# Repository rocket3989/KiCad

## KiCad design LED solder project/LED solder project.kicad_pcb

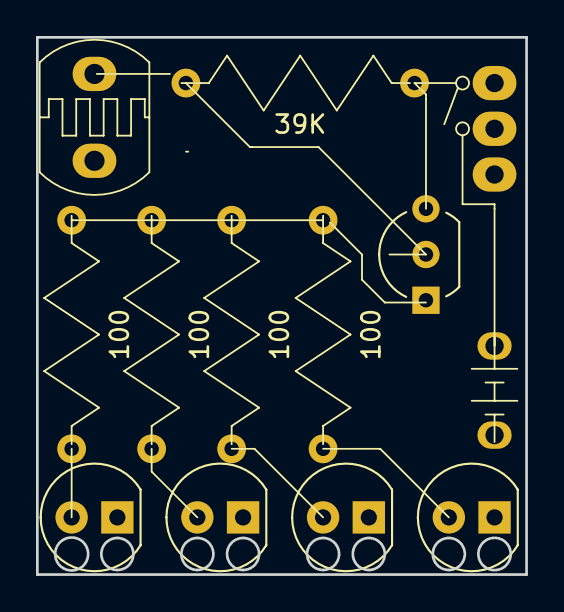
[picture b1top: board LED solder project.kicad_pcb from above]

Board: 2 copper layers, 27.2 x 29.8 mm, 13 parts (0 on the bottom side), 9 nets, no tracks yet.

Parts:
39K, 100, 100#2, 100#3, 100#4: R; resistor
BT1: Battery
D1, D2, D3, D4: LED
Q1: PN2222A; transistor
R2: R_PHOTO; Photoresistor
SW1: SW_SPST; Switch

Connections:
GND: BT1.2, D1.1, D2.1, D3.1, R2.2
unnamed: 100.2, D1.2
unnamed: 100#2.2, D2.2
unnamed: 100#3.2, D3.2
unnamed: 100#4.2, D4.2
unnamed: 100.1, 100#2.1, 100#3.1, 100#4.1, Q1.1
unnamed: 39K.1, Q1.2, R2.1
unnamed: 39K.2, Q1.3, SW1.1
VCC: BT1.1, SW1.2

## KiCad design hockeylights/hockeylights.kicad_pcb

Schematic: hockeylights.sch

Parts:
D1: IR204A; LED_D3.0mm
D2: D_Photo; LED_D3.0mm
J1: I2C in; Socket_Strip_Straight_1x04_Pitch2.54mm
J2: I2C out; Socket_Strip_Straight_1x04_Pitch2.54mm
R1, R2: R; R_Axial_DIN0204_L3.6mm_D1.6mm_P5.08mm_Horizontal
U1: ATTINY85-20SU; DIP-8_W7.62mm_Socket_LongPads
U2, U3: WS2812; LED_D5.0mm-4

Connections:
GND: J1.4, J2.4, R1.2, R2.2, U1.4 (GND), U2.2, U3.2
unnamed: D1.1 (K), R1.1
unnamed: D1.2 (A), U1.6 (PB1(MISO/DO/AIN1/OC0B/OC1A/PCINT1))
unnamed: D2.2 (A), R2.1, U1.2 (PB3(XTAL1/CLKI/~OC1B~/ADC3/PCINT3))
unnamed: J1.2, J2.2, U1.5 (PB0(MOSI/DI/SDA/AIN0/OC0A/~OC1A~/AREF/P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)
unnamed: J1.3, J2.3, U1.7 (PB2(SCK/USCK/SCL/T0/INT0/ADC1/PCINT2))
unnamed: U1.3 (PB4(XTAL2/CLKO/OC1B/ADC2/PCINT4)), U2.1
unnamed: U2.4, U3.1
VCC: D2.1 (K), J1.1, J2.1, U1.8 (VCC), U2.3, U3.3

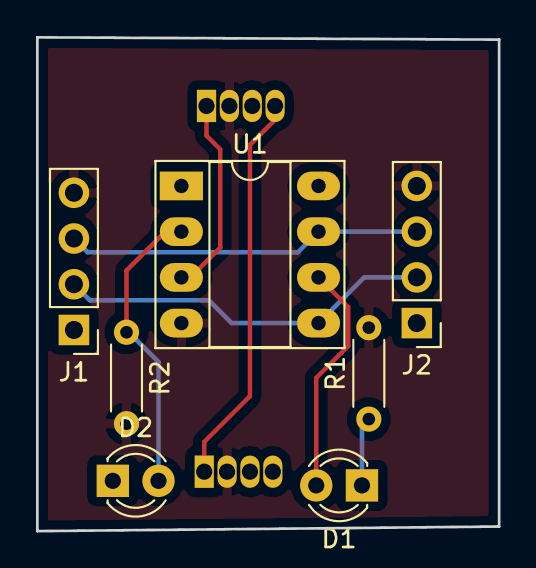
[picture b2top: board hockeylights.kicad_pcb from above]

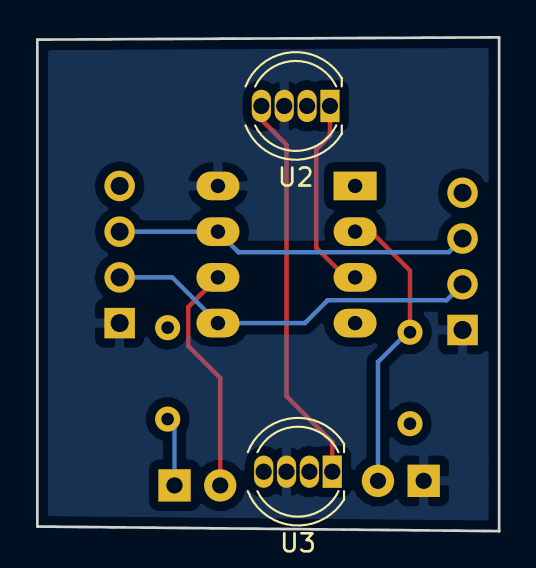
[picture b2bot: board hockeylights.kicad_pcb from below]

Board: 2 copper layers, 25.7 x 27.4 mm, 9 parts (2 on the bottom side), 9 nets.

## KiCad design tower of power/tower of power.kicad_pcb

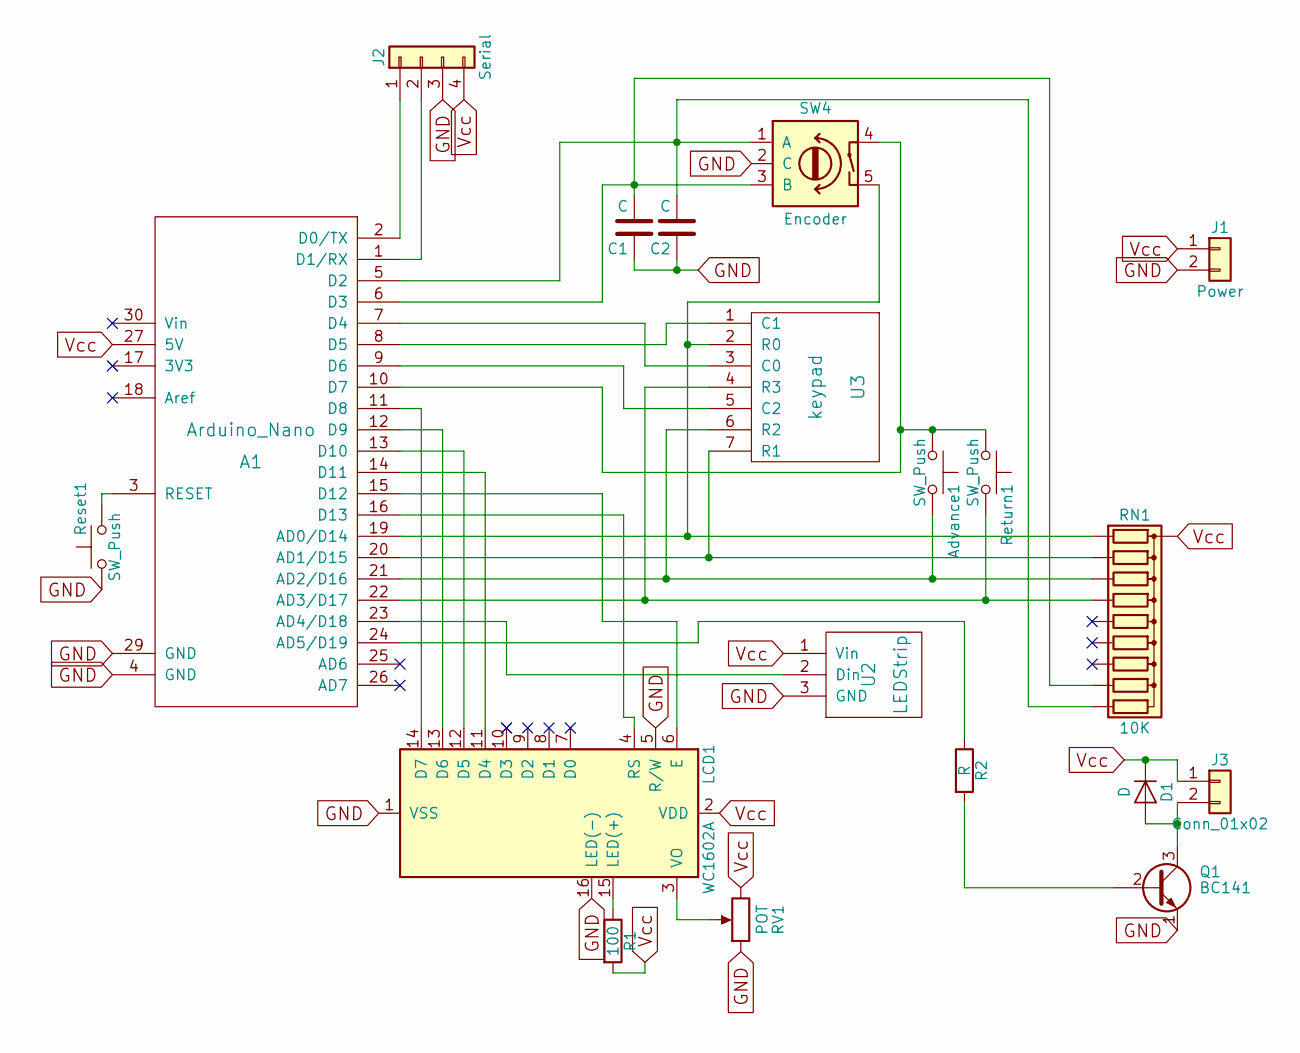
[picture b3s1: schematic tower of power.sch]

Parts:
A1: Arduino_Nano
Advance1: SW_Push; SW_PUSH-12mm
C1, C2: C; C_Disc_D5.0mm_W2.5mm_P5.00mm
D1: D; D_A-405_P7.62mm_Horizontal
J1: Power; Socket_Strip_Straight_1x02_Pitch2.54mm
J2: Serial; Pin_Header_Straight_1x04_Pitch2.54mm
J3: Conn_01x02; Pin_Header_Straight_1x02_Pitch2.54mm
LCD1: WC1602A
Q1: BC141; TO-92_Inline_Wide
R1: 100; R_Axial_DIN0204_L3.6mm_D1.6mm_P5.08mm_Horizontal
R2: R; R_Axial_DIN0207_L6.3mm_D2.5mm_P7.62mm_Horizontal
RN1: 10K; R_Array_SIP10
RV1: POT; Potentiometer_Trimmer_Vishay_T73YP_Horizontal
Reset1: SW_Push; SW_PUSH_6mm_h4.3mm
Return1: SW_Push; SW_PUSH-12mm
SW4: Encoder
U2: LEDStrip; Pin_Header_Straight_1x03_Pitch2.54mm
U3: keypad; KEYPAD

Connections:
GND: A1.4 (GND), A1.29 (GND), C1.1, C2.1, J1.2, J2.3, LCD1.1 (VSS), LCD1.5 (R/W), LCD1.16 (LED(-)), Q1.1 (E), RV1.1, Reset1.1, SW4.2 (C), U2.3 (GND)
unnamed: A1.1 (D1/RX), J2.2
unnamed: A1.2 (D0/TX), J2.1
unnamed: A1.3 (RESET), Reset1.2
unnamed: A1.5 (D2), C2.2, RN1.10 (R9), SW4.1 (A)
unnamed: A1.6 (D3), C1.2, RN1.9 (R8), SW4.3 (B)
unnamed: A1.7 (D4), U3.3 (C0)
unnamed: A1.8 (D5), U3.1 (C1)
unnamed: A1.9 (D6), U3.5 (C2)
unnamed: A1.10 (D7), Advance1.1, Return1.1, SW4.4
unnamed: A1.11 (D8), LCD1.14 (D7)
unnamed: A1.12 (D9), LCD1.13 (D6)
unnamed: A1.13 (D10), LCD1.12 (D5)
unnamed: A1.14 (D11), LCD1.11 (D4)
unnamed: A1.15 (D12), LCD1.6 (E)
unnamed: A1.16 (D13), LCD1.4 (RS)
unnamed: A1.19 (AD0/D14), RN1.2 (R1), SW4.5, U3.2 (R0)
unnamed: A1.20 (AD1/D15), RN1.3 (R2), U3.7 (R1)
unnamed: A1.21 (AD2/D16), Advance1.2, RN1.4 (R3), U3.6 (R2)
unnamed: A1.22 (AD3/D17), RN1.5 (R4), Return1.2, U3.4 (R3)
unnamed: A1.23 (AD4/D18), U2.2 (Din)
unnamed: A1.24 (AD5/D19), R2.1
unnamed: D1.2 (A), J3.2, Q1.3 (C)
unnamed: LCD1.3 (VO), RV1.2
unnamed: LCD1.15 (LED(+)), R1.1
unnamed: Q1.2 (B), R2.2
Vcc: A1.27 (5V), D1.1 (K), J1.1, J2.4, J3.1, LCD1.2 (VDD), R1.2, RN1.1 (common), RV1.3, U2.1 (Vin)

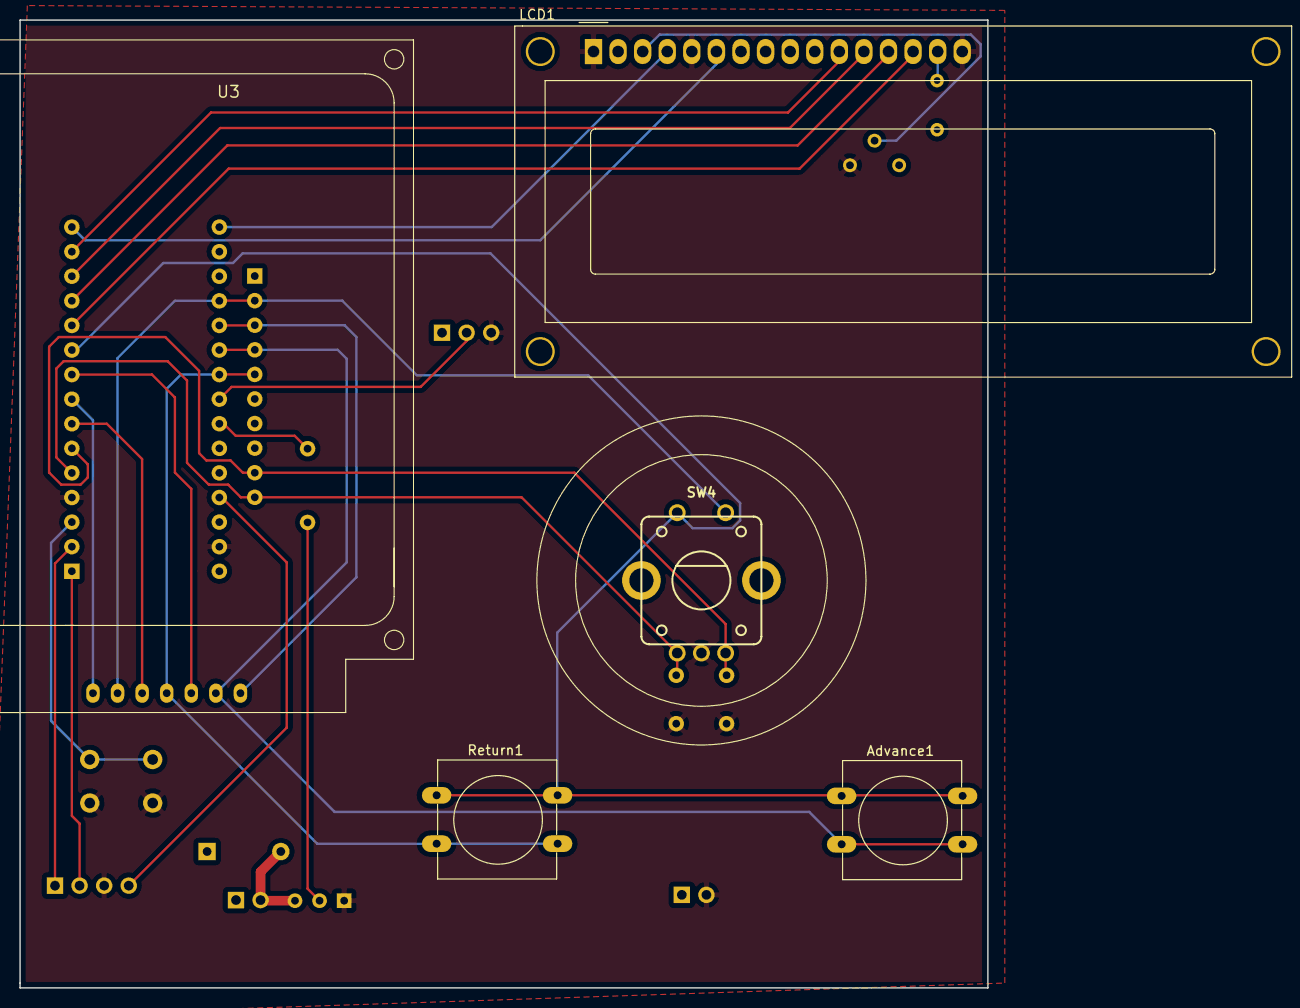
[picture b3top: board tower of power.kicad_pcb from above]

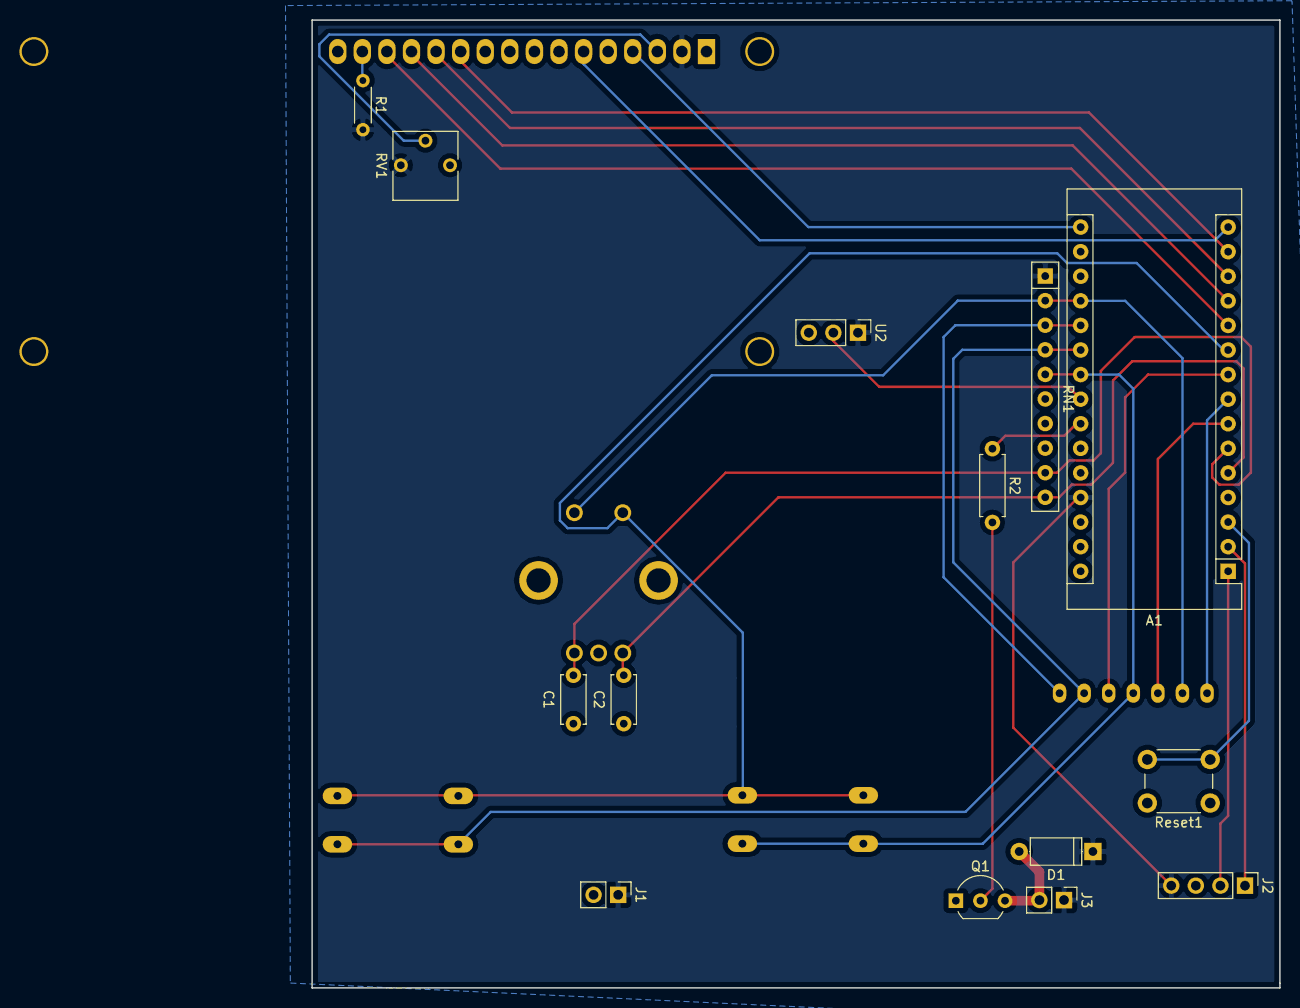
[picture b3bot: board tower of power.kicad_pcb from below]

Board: 2 copper layers, 100.0 x 100.0 mm, 19 parts (14 on the bottom side), 27 nets.

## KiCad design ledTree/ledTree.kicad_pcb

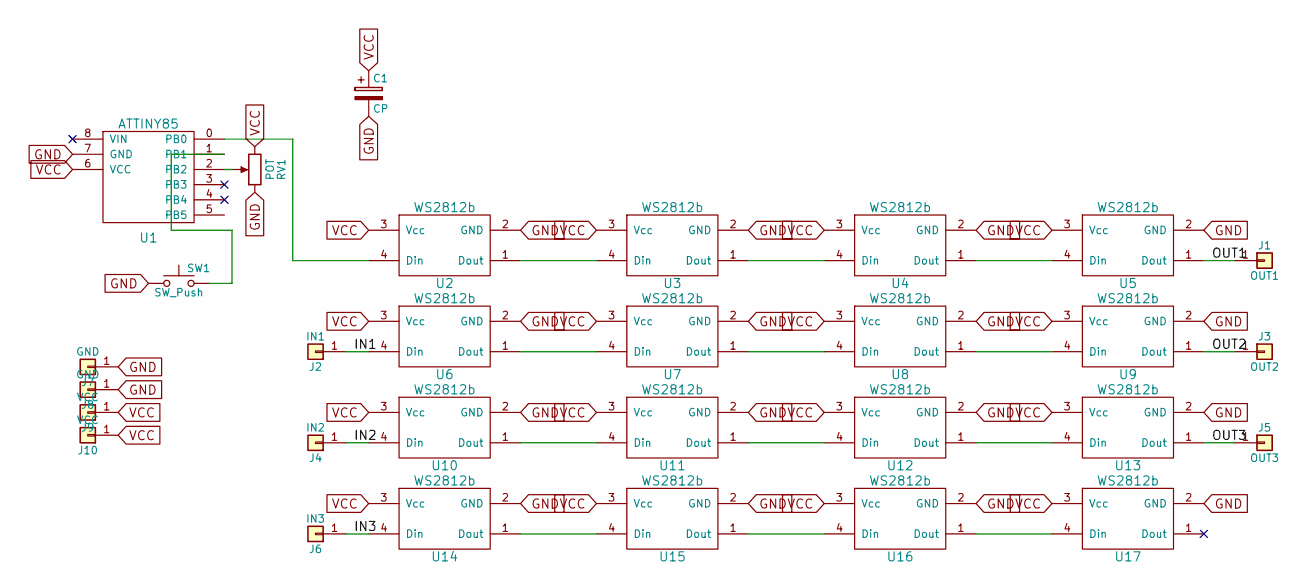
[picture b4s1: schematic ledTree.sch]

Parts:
C1: CP; CP_Radial_D5.0mm_P2.50mm
J1: OUT1; Pin_d0.9mm_L10.0mm_W2.4mm_FlatFork
J2: IN1; Pin_d0.9mm_L10.0mm_W2.4mm_FlatFork
J3: OUT2; Pin_d0.9mm_L10.0mm_W2.4mm_FlatFork
J4: IN2; Pin_d0.9mm_L10.0mm_W2.4mm_FlatFork
J5: OUT3; Pin_d0.9mm_L10.0mm_W2.4mm_FlatFork
J6: IN3; Pin_d0.9mm_L10.0mm_W2.4mm_FlatFork
J7, J8: GND; Pin_d0.9mm_L10.0mm_W2.4mm_FlatFork
J9, J10: VCC; Pin_d0.9mm_L10.0mm_W2.4mm_FlatFork
RV1: POT; Potentiometer_Trimmer_Bourns_3339S_Vertical
SW1: SW_Push; SW_PUSH_6mm
U1: ATTINY85
U2, U3, U4, U5, U6, U7, U8, U9, U10, U11, U12, U13, U14, U15, U16, U17: WS2812b; LED_D5.0mm-4

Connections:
/IN1: J2.1, U6.4 (Din)
/IN2: J4.1, U10.4 (Din)
/IN3: J6.1, U14.4 (Din)
/OUT1: J1.1, U5.1 (Dout)
/OUT2: J3.1, U9.1 (Dout)
/OUT3: J5.1, U13.1 (Dout)
GND: C1.2, J7.1, J8.1, RV1.1, SW1.1, U1.7 (GND), U2.2 (GND), U3.2 (GND), U4.2 (GND), U5.2 (GND), U6.2 (GND), U7.2 (GND), U8.2 (GND), U9.2 (GND), U10.2 (GND), U11.2 (GND), U12.2 (GND), U13.2 (GND), U14.2 (GND), U15.2 (GND), U16.2 (GND), U17.2 (GND); also elsewhere on the board
unnamed 7: RV1.2, U1.2 (PB2); also elsewhere on the board
unnamed: SW1.2, U1.1 (PB1)
unnamed: U1.0 (PB0), U2.4 (Din)
unnamed: U2.1 (Dout), U3.4 (Din)
unnamed: U3.1 (Dout), U4.4 (Din)
unnamed: U4.1 (Dout), U5.4 (Din)
unnamed: U6.1 (Dout), U7.4 (Din)
unnamed: U7.1 (Dout), U8.4 (Din)
unnamed: U8.1 (Dout), U9.4 (Din)
unnamed: U10.1 (Dout), U11.4 (Din)
unnamed: U11.1 (Dout), U12.4 (Din)
unnamed: U12.1 (Dout), U13.4 (Din)
unnamed: U14.1 (Dout), U15.4 (Din)
unnamed: U15.1 (Dout), U16.4 (Din)
unnamed: U16.1 (Dout), U17.4 (Din)
VCC: C1.1, J9.1, J10.1, RV1.3, U1.6 (VCC), U2.3 (Vcc), U3.3 (Vcc), U4.3 (Vcc), U5.3 (Vcc), U6.3 (Vcc), U7.3 (Vcc), U8.3 (Vcc), U9.3 (Vcc), U10.3 (Vcc), U11.3 (Vcc), U12.3 (Vcc), U13.3 (Vcc), U14.3 (Vcc), U15.3 (Vcc), U16.3 (Vcc), U17.3 (Vcc); also elsewhere on the board

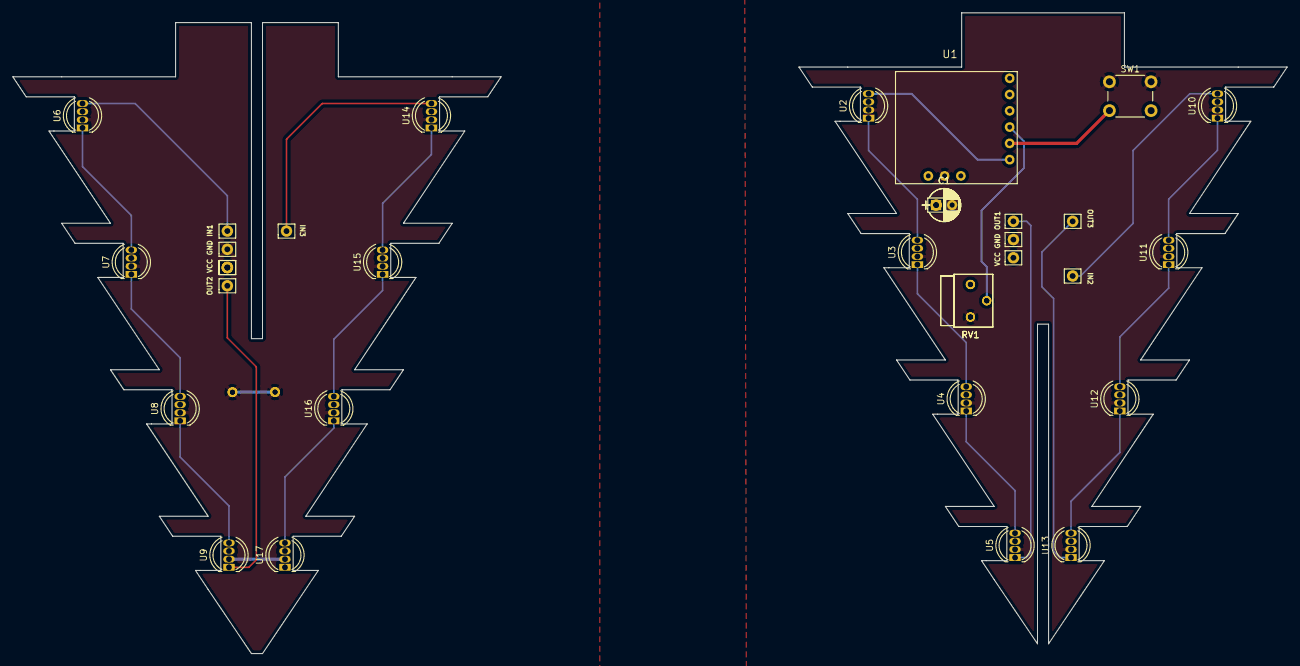
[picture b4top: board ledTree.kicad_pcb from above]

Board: 2 copper layers, 198.9 x 100.0 mm, 33 parts (0 on the bottom side), 23 nets.

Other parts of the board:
C1#2: CP; CP_Radial_D5.0mm_P2.50mm
J10#2: VCC; Pin_d0.9mm_L10.0mm_W2.4mm_FlatFork
RV1#2: POT; Potentiometer_Trimmer_Bourns_3339S_Vertical

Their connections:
GND: C1#2.1, RV1#2.1; also elsewhere on the board
unnamed 7: RV1#2.2; also elsewhere on the board
VCC: J10#2.1, RV1#2.3; also elsewhere on the board

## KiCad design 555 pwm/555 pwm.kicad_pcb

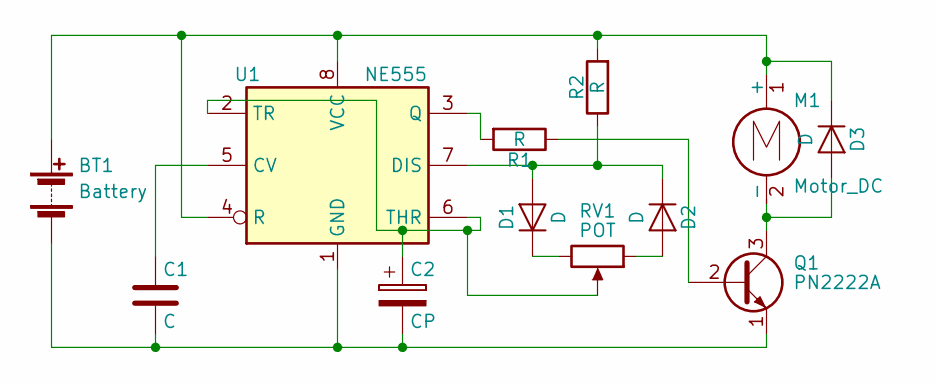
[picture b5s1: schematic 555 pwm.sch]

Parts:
BT1: Battery; GTK2400-V2
C1: C; C_Disc_D3.8mm_W2.6mm_P2.50mm
C2: CP; CP_Radial_D5.0mm_P2.50mm
D1, D2, D3: D; D_A-405_P10.16mm_Horizontal
M1: Motor_DC; TerminalBlock_bornier-2_P5.08mm
Q1: PN2222A; TO-92_Inline_Wide
R1, R2: R; R_Axial_DIN0207_L6.3mm_D2.5mm_P7.62mm_Horizontal
RV1: POT; Potentiometer_Alps_RK163_Single_Vertical
U1: NE555; DIP-8_W7.62mm_Socket

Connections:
unnamed: BT1.1 (+), D3.1 (K), M1.1 (+), R2.2, U1.4 (R), U1.8 (VCC)
unnamed: BT1.2 (-), C1.2, C2.2, Q1.1 (E), U1.1 (GND)
unnamed: C1.1, U1.5 (CV)
unnamed: C2.1, RV1.2, U1.2 (TR), U1.6 (THR)
unnamed: D1.1 (K), RV1.3
unnamed: D1.2 (A), D2.1 (K), R2.1, U1.7 (DIS)
unnamed: D2.2 (A), RV1.1
unnamed: D3.2 (A), M1.2 (-), Q1.3 (C)
unnamed: Q1.2 (B), R1.1
unnamed: R1.2, U1.3 (Q)

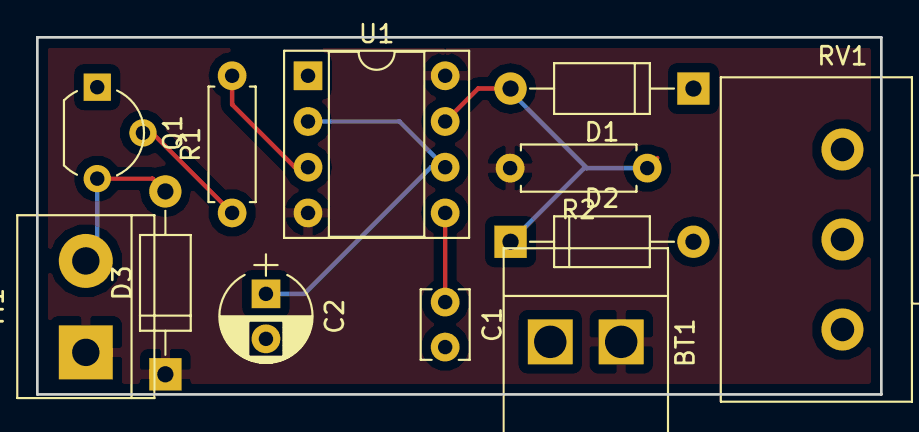
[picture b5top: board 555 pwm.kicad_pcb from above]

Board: 2 copper layers, 46.9 x 19.8 mm, 12 parts (0 on the bottom side), 10 nets.

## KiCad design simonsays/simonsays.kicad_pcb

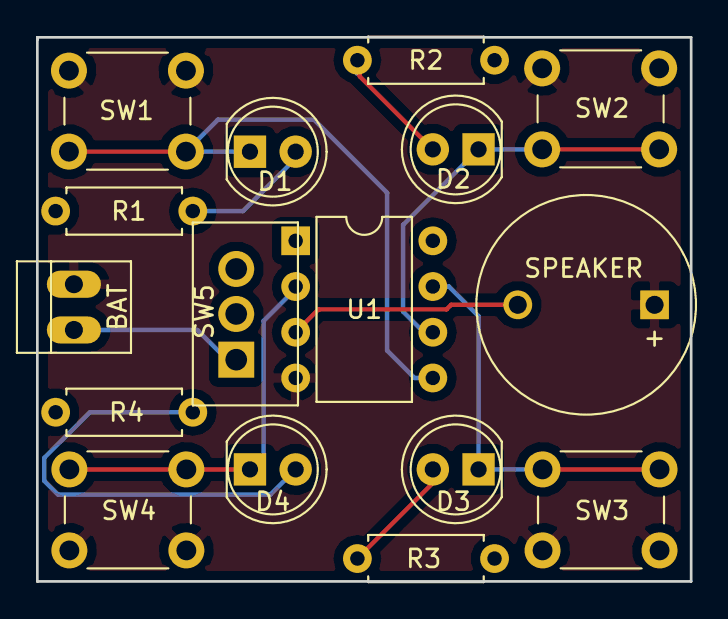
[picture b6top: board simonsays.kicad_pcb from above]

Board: 2 copper layers, 36.3 x 30.2 mm, 16 parts (0 on the bottom side), 12 nets.

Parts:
BAT: Battery; PINHEAD1-2
D1, D2, D3, D4: LED; LED_D5.0mm
R1, R2, R3, R4: R; R_Axial_DIN0207_L6.3mm_D2.5mm_P7.62mm_Horizontal
SPEAKER: Speaker; MagneticBuzzer_ProSignal_ABI-009-RC
SW1: SW_DIP_x01; SW_PUSH_6mm_h5mm
SW2, SW3, SW4: SW_DIP_x01; SW_PUSH_6mm_h9.5mm
SW5: SW_DIP_x01; Wafer_Vertical10x5.8x7RM2.5-3
U1: ATTINY85-20PU; DIP-8_W7.62mm

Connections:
GND: BAT.2, SPEAKER.1, SW1.2, SW2.2, SW3.2, SW4.2, U1.4
unnamed: BAT.1, SW5.1
unnamed: D1.1, SW1.1, U1.5
unnamed: D1.2, R1.2
unnamed: D2.1, SW2.1, U1.6
unnamed: D2.2, R2.2
unnamed: D3.1, SW3.1, U1.7
unnamed: D3.2, R3.2
unnamed: D4.1, SW4.1, U1.2
unnamed: D4.2, R4.2
unnamed: SPEAKER.2, U1.3
unnamed: R1.1, R2.1, R3.1, R4.1, SW5.2, U1.8

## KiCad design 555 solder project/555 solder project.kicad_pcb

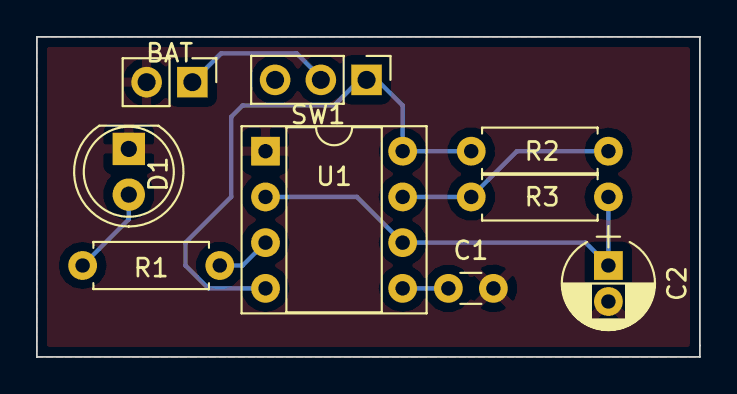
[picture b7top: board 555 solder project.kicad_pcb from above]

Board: 2 copper layers, 36.8 x 17.8 mm, 9 parts (0 on the bottom side), 8 nets.

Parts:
BAT: Battery; Pin_Header_Straight_1x02_Pitch2.54mm
C1: C; C_Disc_D3.0mm_W1.6mm_P2.50mm
C2: CP; CP_Radial_D5.0mm_P2.00mm
D1: LED; LED_D5.0mm_FlatTop
R1, R2, R3: R; R_Axial_DIN0207_L6.3mm_D2.5mm_P7.62mm_Horizontal
SW1: SW_DIP_x01; Pin_Header_Straight_1x03_Pitch2.54mm
U1: NE555; DIP-8_W7.62mm_Socket

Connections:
GND: BAT.2, C1.2, C2.2, D1.1, U1.1
unnamed: BAT.1, SW1.2
unnamed: C1.1, U1.5
unnamed: C2.1, R3.2, U1.2, U1.6
unnamed: D1.2, R1.2
unnamed: R1.1, U1.3
unnamed: R2.1, SW1.1, U1.4, U1.8
unnamed: R2.2, R3.1, U1.7

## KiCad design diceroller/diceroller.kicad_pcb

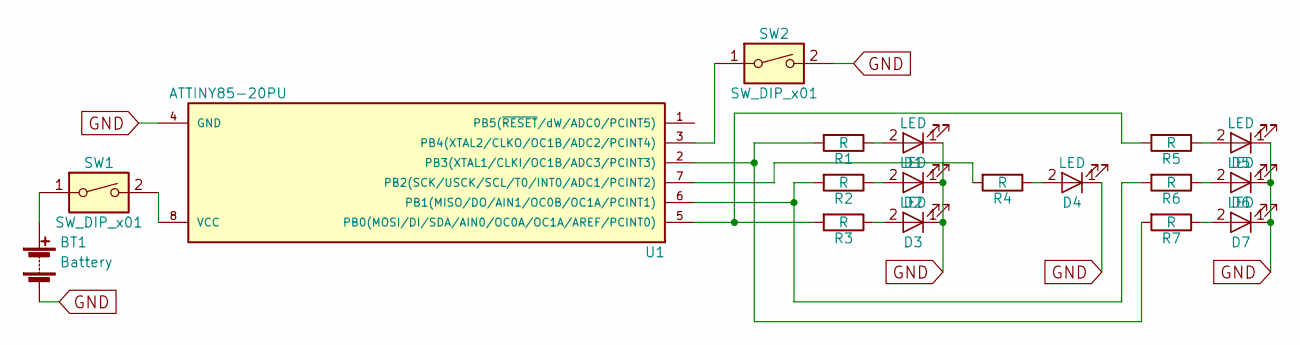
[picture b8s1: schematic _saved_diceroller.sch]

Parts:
BT1: Battery; PINHEAD1-2
D1, D2, D3, D4, D5, D6, D7: LED; LED_D5.0mm_FlatTop
R1, R2, R3, R4, R5, R6, R7: R; R_Axial_DIN0207_L6.3mm_D2.5mm_P7.62mm_Horizontal
SW1: SW_DIP_x01; Wafer_Vertical10x5.8x7RM2.5-3
SW2: SW_DIP_x01; SW_PUSH_6mm_h5mm
U1: ATTINY85-20PU; DIP-8_W7.62mm_LongPads

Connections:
GND: BT1.2 (-), D1.1 (K), D2.1 (K), D3.1 (K), D4.1 (K), D5.1 (K), D6.1 (K), D7.1 (K), SW2.2, U1.4 (GND); also elsewhere on the board
unnamed 1: BT1.1 (+), SW1.1; also elsewhere on the board
unnamed: D1.2 (A), R1.1
unnamed: D2.2 (A), R2.1
unnamed: D3.2 (A), R3.1
unnamed: D4.2 (A), R4.1
unnamed: D5.2 (A), R5.1
unnamed: D6.2 (A), R6.1
unnamed: D7.2 (A), R7.1
unnamed: R1.2, R7.2, U1.2 (PB3(XTAL1/CLKI/OC1B/ADC3/PCINT3))
unnamed: R2.2, R6.2, U1.6 (PB1(MISO/DO/AIN1/OC0B/OC1A/PCINT1))
unnamed: R3.2, R5.2, U1.5 (PB0(MOSI/DI/SDA/AIN0/OC0A/OC1A/AREF/PCI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)
unnamed: R4.2, U1.7 (PB2(SCK/USCK/SCL/T0/INT0/ADC1/PCINT2))
unnamed: SW1.2, U1.8 (VCC)
unnamed: SW2.1, U1.3 (PB4(XTAL2/CLKO/OC1B/ADC2/PCINT4))

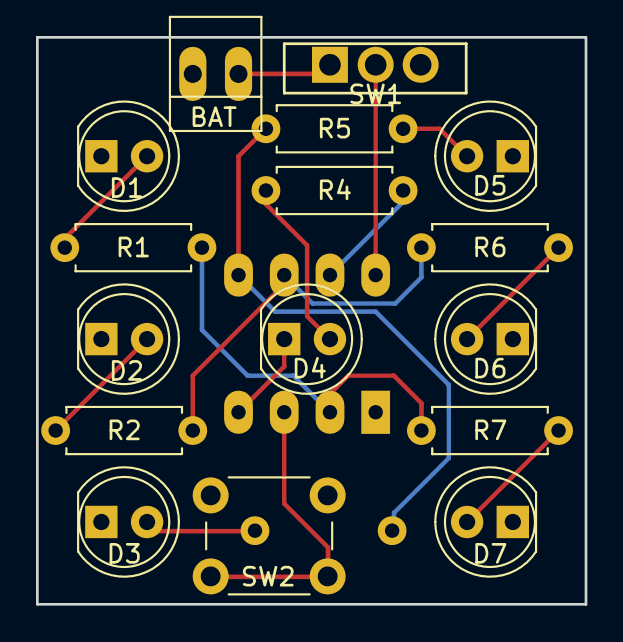
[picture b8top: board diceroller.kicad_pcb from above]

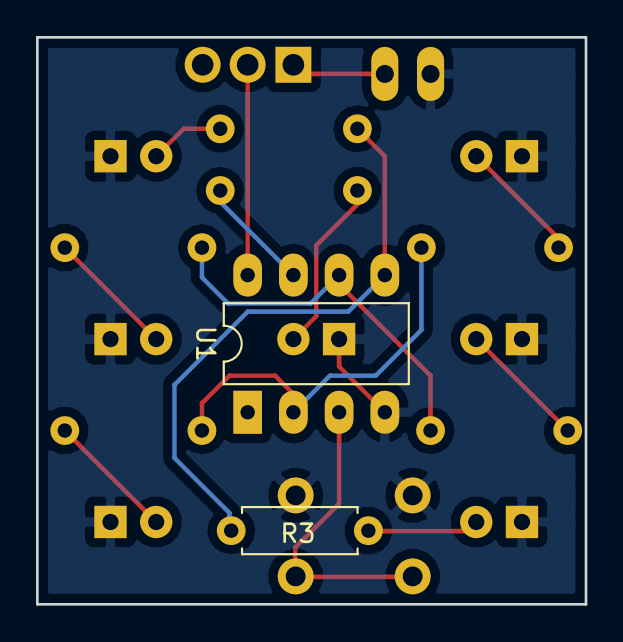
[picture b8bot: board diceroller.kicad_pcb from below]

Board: 2 copper layers, 30.5 x 31.5 mm, 18 parts (2 on the bottom side), 15 nets.

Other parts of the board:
BAT: Battery; PINHEAD1-2

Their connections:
GND: BAT.2; also elsewhere on the board
unnamed 1: BAT.1; also elsewhere on the board

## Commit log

2017-11-30 adding all files
2017-11-30 updating files
2017-12-01 adding computer files
2017-12-01 adding alu 4 bit
2017-12-01 oops fixed 4-bit connection
2017-12-01 computer changes
2017-12-02 adding led tree
2017-12-03 finished tree!
2017-12-03 test
2018-01-08 updates?
2018-01-31 many updates
2018-01-31 additions
2018-03-06 updatearro
2018-03-11 finished tower maybe
2018-03-15 added many
2018-04-17 saved the tree
2018-12-08 circuits ordered
